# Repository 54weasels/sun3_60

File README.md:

# Homebrew Sun 3/60

This project reproduces the Sun 3/60 computer from available schematics such as https://www.sun3arc.org/schematics/3_60/index.phtml

At the moment:
- only implementing the min required 4mb of RAM
- left out the SCSI and Video sections
- only put in the serial controller for A/B, left out the keyboard/mouse
- TTL serial, I didn't implement full rs232 or modem support
- left out the coax ethernet entirely
- no FPU

The board can boot a standard boot PROM (using version XXX for development), as well as netboot SunOS 4.1.1 and NetBSD10.
NetBSD with a GENERIC kernel is not really functional because of the 4MB of RAM and swap over network.

Current version is a 4-layer board - check the build/version log in the production directory for known issues.

## TODO
- For the current board layout, at a high level
  - add more RAM - either moving to 4MB 30-pin SIMMs, or redesign around 72-pin SIMMs, or both
  - replace a few unobtainium or exceedingly cumbersome components like the bipolar PROM for the idprom
- Moving to a new layout, can add a lot more in
  - FPU
  - SCSI
  - decide on whether or not to put in video, and which one. If video goes in then so should the missing keyboard/mouse serial controller.
- Some more modernization is possible
  - add an on-board twisted pair transciever and RJ45 port
- If things really are going well, in the long term whole swaths of the low-density logic and PALs can be replaced with a/few CPLDs.

## FAQ
- What was this designed in, layers, etc?
  - This was done in KiCAD and it's a 4-layer board. It helped to have the signals easily accessible on the top and bottom to do critical fixes.
- Where is storage, and can we get some modern solution?
  - SCSI is next, but is quite big and will increase the board size by ~20%. SCSI-to-SD can be used easily. More fancy solutionsl like SCSI-to-SATA are not likely to happen.
- Can we get rid of the PALs?
  - YES, see the note on the [PAL page](pal/Readme.md)
- How about FPGAs?
  - Most likely not.
- What's the deal with video?
  - The framebuffer available in the schematics is both a bottom shelf BW, main-RAM-stealing all-in-software deal, and ECL levels on top of it. While getting it to do VGA levels is probably not that hard, it's goint to be a really bad solution overall.
  - Ideally we can get the schematics for the P4 CG4(6?) which is color and much better overall. It may be possible to reverse-engineer an existing board without the schematics, but I'm not going to do so with the only working board I have - I'll gladly buy another one to experiment with, if one was available.
- Where's the VME bus?
  - There never was a VME bus on the 3/60. It might be possible to add one, depending on how complete the various PALs are. It's unlikely due to not really having anything to add in that's not already there (Ethernet, SCSI, RAM) so unless there's a plentiful and amazing VME video card, this is not a priority.
- How about surface mount components where available, more modernization?
  - Sure! the initial implementation/layout/component choice was entirely driven by trying to be as close to the original as possible, so it's easier to debug when things go south, which they did. As the design stabilizes, it's possible to compress quite a bit, including going to higher layer count board, consolidating components like the static ram for the MMU into wider variants, etc.
- How about a processor upgrade?
  - While the original 3/60 board has room for a 68030, it's wired to run exclusively in '020 compatibility mode, and there is no way to get the built-in MMU to work.
  - It's possible to boost the main clock substantially (50Mhz which is divided by two for the CPU resulting in 25Mhz) and still have a stable system. The core design is pretty asynchronous so it might also be possible to run the RAM/etc at slower speed and run the processor faster (as you can do on the 3/80 by splitting the FPU and CPU clocks for example), but it hasn't been tried yet. It will not yield substantial improvements however.

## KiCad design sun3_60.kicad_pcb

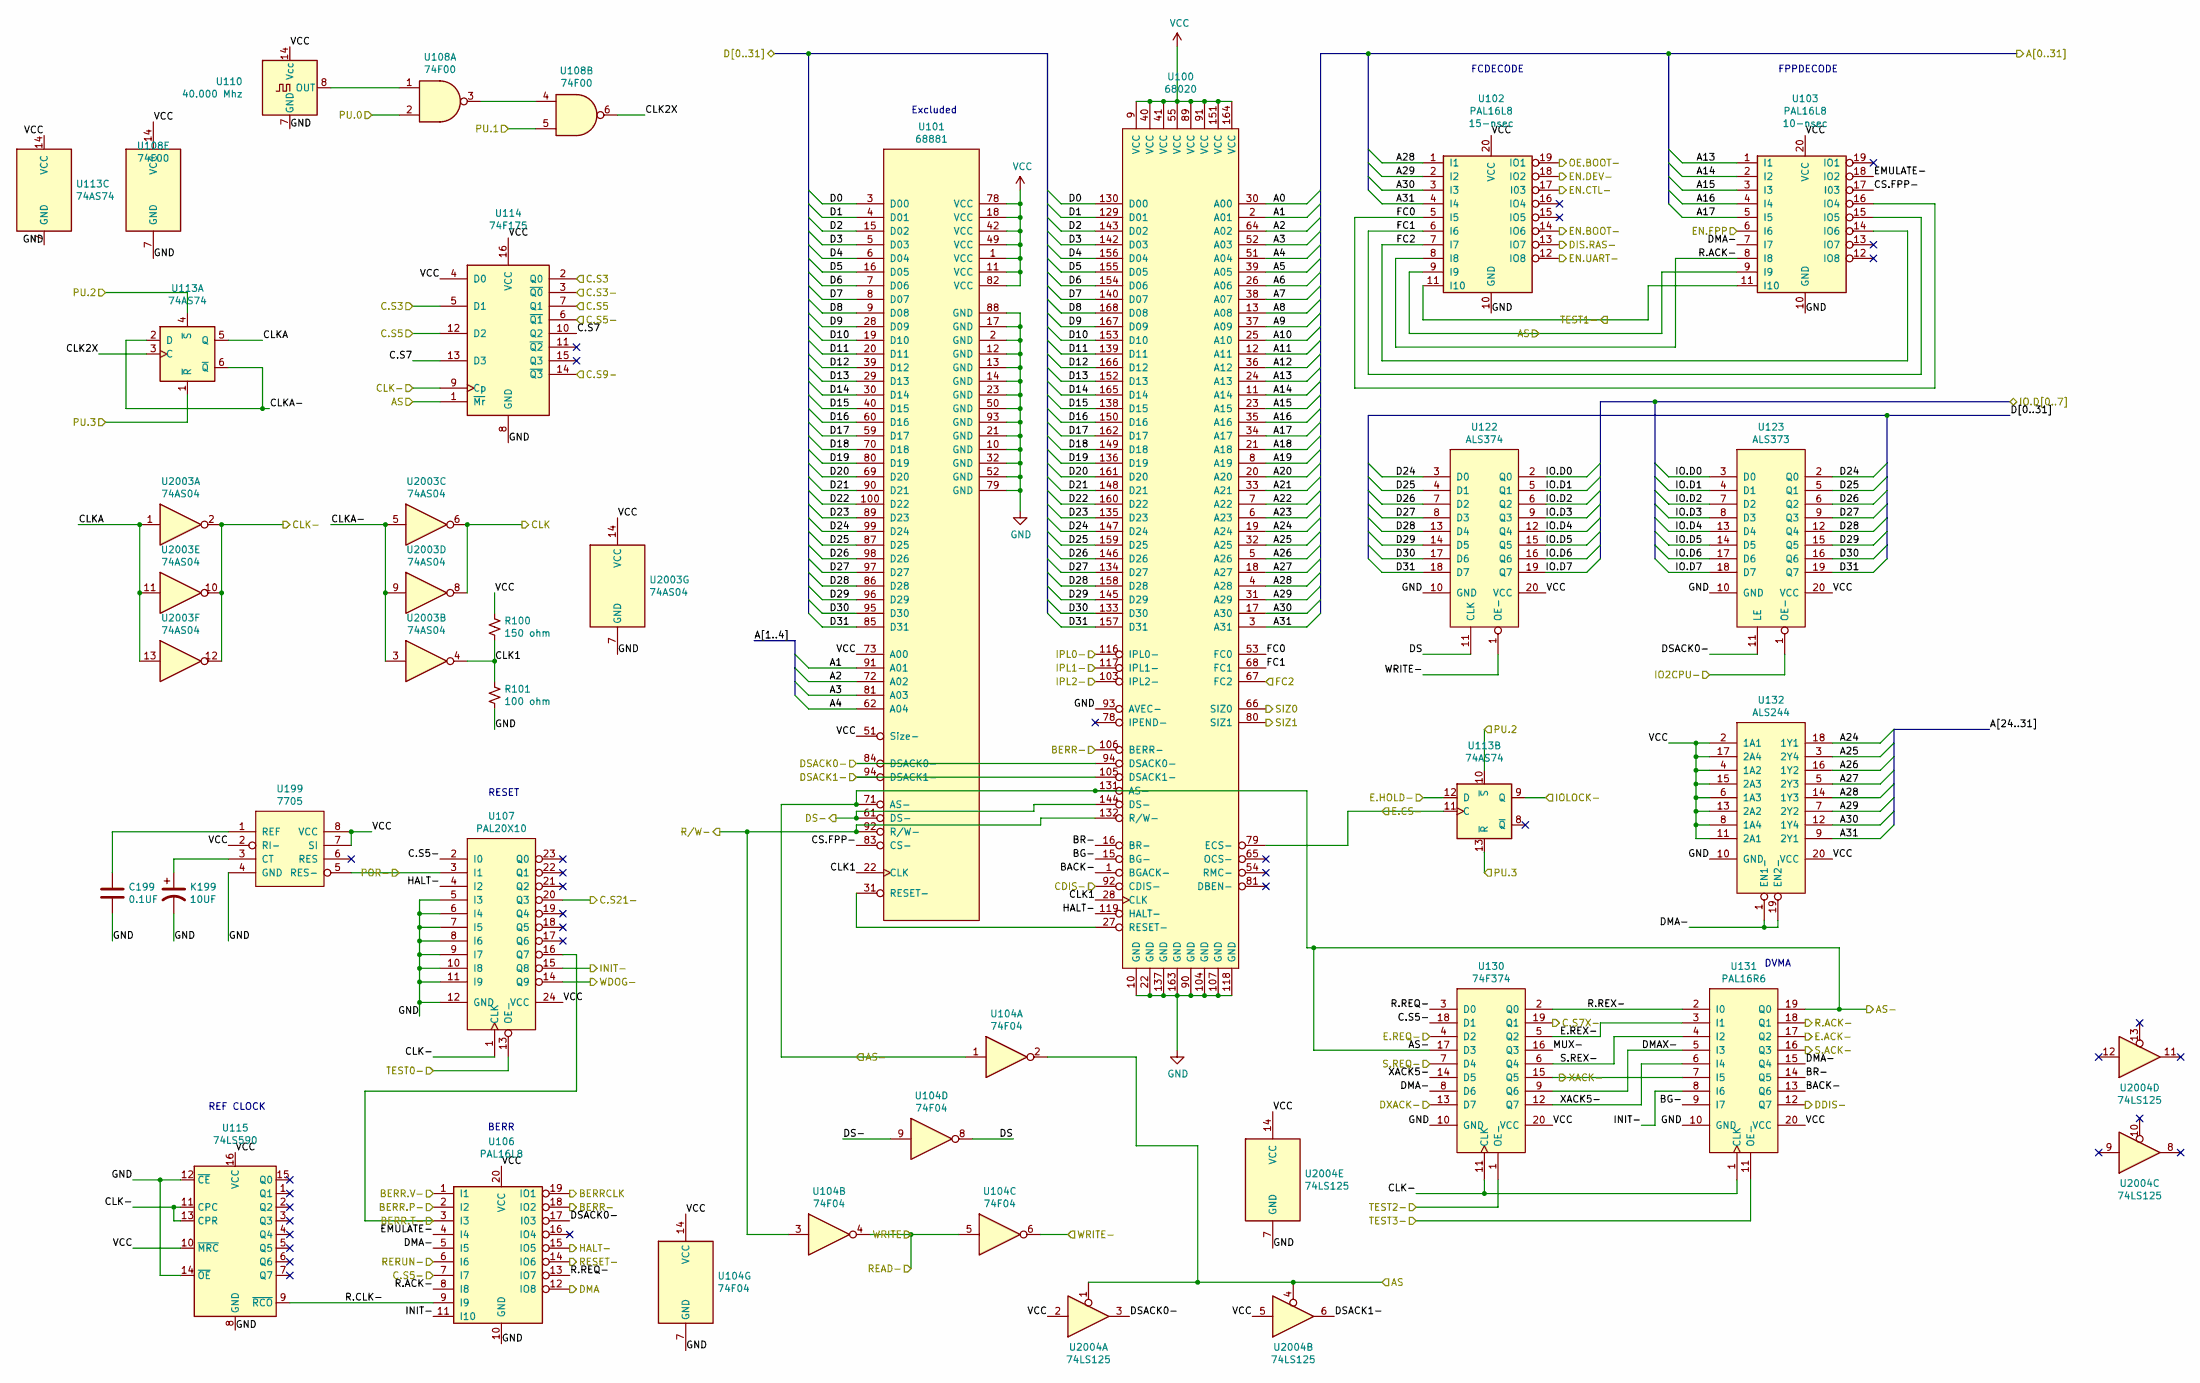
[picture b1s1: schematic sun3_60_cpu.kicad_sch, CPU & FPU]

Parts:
C199: 0.1UF; C_Disc_D3.0mm_W2.0mm_P2.50mm
K199: 10UF; CP_Radial_D10.0mm_P5.00mm
R100: 150 ohm; R_Axial_DIN0207_L6.3mm_D2.5mm_P7.62mm_Horizontal
R101: 100 ohm; R_Axial_DIN0207_L6.3mm_D2.5mm_P7.62mm_Horizontal
U100: 68020
U101: 68881
U102, U103, U106: PAL16L8; DIP-20_W7.62mm
U104: 74F04; DIP-14_W7.62mm
U107: PAL20X10; DIP-24_W7.62mm
U108: 74F00; DIP-14_W7.62mm
U110: 40.000 Mhz; Oscillator_DIP-14
U113: 74AS74; DIP-14_W7.62mm
U114: 74F175; DIP-16_W7.62mm
U115: 74LS590; DIP-16_W7.62mm
U122: ALS374; ALS373
U123: ALS373
U130: 74F374; DIP-20_W7.62mm
U131: PAL16R6; DIP-20_W7.62mm
U132: ALS244; DIP-20_W7.62mm
U199: 7705; DIP-8_W7.62mm
U2003: 74AS04; DIP-14_W7.62mm
U2004: 74LS125; DIP-14_W7.62mm

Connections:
/AS: U102.9 (I9), U103.9 (I9), U104.2, U114.1 (~Mr), U2004.1, U2004.4; also elsewhere on the board
/AS-: U100.131 (AS-), U101.71 (AS-), U104.1, U130.17 (D3), U131.19 (Q0); also elsewhere on the board
/BERR-: U100.106 (BERR-), U106.18 (IO2); also elsewhere on the board
/C.S3: U114.2 (Q0), U114.5 (D1); also elsewhere on the board
/C.S3-: U114.3 (~Q0); also elsewhere on the board
/C.S5: U114.7 (Q1), U114.12 (D2); also elsewhere on the board
/CDIS-: U100.92 (CDIS-); also elsewhere on the board
/CLK: U2003.6, U2003.8; also elsewhere on the board
/CLK-: U107.1 (CLK), U114.9 (Cp), U115.11 (CPC), U115.13 (CPR), U130.11 (CLK), U131.1 (CLK), U2003.2, U2003.10, U2003.12; also elsewhere on the board
/DDIS-: U131.12 (Q7); also elsewhere on the board
/DIS.RAS-: U102.13 (IO7); also elsewhere on the board
/DMA: U106.12 (IO8); also elsewhere on the board
/DS-: U100.144 (DS-), U101.61 (DS-), U104.9; also elsewhere on the board
/DSACK0-: U100.94 (DSACK0-), U101.84 (DSACK0-), U106.17 (I03), U123.11 (LE), U2004.3; also elsewhere on the board
/DSACK1-: U100.105 (DSACK1-), U101.94 (DSACK1-), U2004.6; also elsewhere on the board
/DXACK-: U130.13 (D7); also elsewhere on the board
/E.ACK-: U131.17 (Q2); also elsewhere on the board
/E.CS-: U100.79 (ECS-), U113.11 (C); also elsewhere on the board
/E.HOLD-: U113.12 (D); also elsewhere on the board
/E.REQ-: U130.4 (D2); also elsewhere on the board
/EN.DEV-: U102.18 (IO2); also elsewhere on the board
/EN.UART-: U102.12 (IO8); also elsewhere on the board
/Ethernet/A0: U100.30 (A00); also elsewhere on the board
/Ethernet/A1: U100.2 (A01), U101.91 (A01); also elsewhere on the board
/Ethernet/A2: U100.64 (A02), U101.72 (A02); also elsewhere on the board
/Ethernet/A3: U100.52 (A03), U101.81 (A03); also elsewhere on the board
/Ethernet/A4: U100.51 (A04), U101.62 (A04); also elsewhere on the board
/Ethernet/A5: U100.39 (A05); also elsewhere on the board
/Ethernet/A6: U100.26 (A06); also elsewhere on the board
/Ethernet/A7: U100.38 (A07); also elsewhere on the board
/Ethernet/A8: U100.13 (A08); also elsewhere on the board
/Ethernet/A9: U100.37 (A09); also elsewhere on the board
/Ethernet/A10: U100.25 (A10); also elsewhere on the board
/Ethernet/A11: U100.12 (A11); also elsewhere on the board
/Ethernet/A12: U100.36 (A12); also elsewhere on the board
/Ethernet/A13: U100.24 (A13), U103.1 (I1); also elsewhere on the board
/Ethernet/A14: U100.11 (A14), U103.2 (I2); also elsewhere on the board
/Ethernet/A15: U100.23 (A15), U103.3 (I3); also elsewhere on the board
/Ethernet/A16: U100.35 (A16), U103.4 (I4); also elsewhere on the board
/Ethernet/A17: U100.34 (A17), U103.5 (I5); also elsewhere on the board
/Ethernet/A18: U100.21 (A18); also elsewhere on the board
/Ethernet/A19: U100.8 (A19); also elsewhere on the board
/Ethernet/A20: U100.20 (A20); also elsewhere on the board
/Ethernet/A21: U100.33 (A21); also elsewhere on the board
/Ethernet/A22: U100.7 (A22); also elsewhere on the board
/Ethernet/A23: U100.6 (A23); also elsewhere on the board
/Ethernet/A24: U100.19 (A24), U132.18 (1Y1); also elsewhere on the board
/Ethernet/A25: U100.32 (A25), U132.3 (2Y4); also elsewhere on the board
/Ethernet/A26: U100.5 (A26), U132.16 (1Y2); also elsewhere on the board
/Ethernet/A27: U100.18 (A27), U132.5 (2Y3); also elsewhere on the board
/Ethernet/A28: U100.4 (A28), U102.1 (I1), U132.14 (1Y3); also elsewhere on the board
/Ethernet/A29: U100.31 (A29), U102.2 (I2), U132.7 (2Y2); also elsewhere on the board
/Ethernet/A30: U100.17 (A30), U102.3 (I3), U132.12 (1Y4); also elsewhere on the board
/Ethernet/A31: U100.3 (A31), U102.4 (I4), U132.9 (2Y1); also elsewhere on the board
/FC2: U100.67 (FC2), U102.7 (I7), U103.14 (IO6); also elsewhere on the board
/HALT-: U100.119 (HALT-), U106.15 (IO5), U107.4 (I2); also elsewhere on the board
/INIT-: U106.11 (I10), U107.15 (Q8), U131.8 (I6); also elsewhere on the board
/IO2CPU-: U123.1 (OE-); also elsewhere on the board
/IOLOCK-: U113.9 (Q); also elsewhere on the board
/IPL0-: U100.116 (IPL0-); also elsewhere on the board
/IPL1-: U100.117 (IPL1-); also elsewhere on the board
/IPL2-: U100.103 (IPL2-); also elsewhere on the board
/POR-: U107.3 (I1), U199.5 (RES-); also elsewhere on the board
/PU0: U108.2; also elsewhere on the board
/PU1: U108.5; also elsewhere on the board
/PU2: U113.4 (~S), U113.10 (~S); also elsewhere on the board
/PU3: U113.1 (~R), U113.13 (~R); also elsewhere on the board
/R.ACK-: U102.8 (I8), U103.8 (I8), U106.8 (I8), U131.18 (Q1); also elsewhere on the board
/READ-: U104.4, U104.5; also elsewhere on the board
/RERUN-: U106.6 (I6); also elsewhere on the board
/RESET-: U106.14 (IO6); also elsewhere on the board
/R/W-: U100.132 (R/W-), U101.92 (R/W-), U104.3; also elsewhere on the board
/SCSI 2, Parity/IO.D0: U122.2 (Q0), U123.3 (D0); also elsewhere on the board
/SCSI 2, Parity/IO.D1: U122.5 (Q1), U123.4 (D1); also elsewhere on the board
/SCSI 2, Parity/IO.D2: U122.6 (Q2), U123.7 (D2); also elsewhere on the board
/SCSI 2, Parity/IO.D3: U122.9 (Q3), U123.8 (D3); also elsewhere on the board
/SCSI 2, Parity/IO.D4: U122.12 (Q4), U123.13 (D4); also elsewhere on the board
/SCSI 2, Parity/IO.D5: U122.15 (Q5), U123.14 (D5); also elsewhere on the board
/SCSI 2, Parity/IO.D6: U122.16 (Q6), U123.17 (D6); also elsewhere on the board
/SCSI 2, Parity/IO.D7: U122.19 (Q7), U123.18 (D7); also elsewhere on the board
/SIZ0: U100.66 (SIZ0); also elsewhere on the board
/SIZ1: U100.80 (SIZ1); also elsewhere on the board
/TEST0-: U107.13 (OE-); also elsewhere on the board
/TEST1-: U102.11 (I10), U103.11 (I10); also elsewhere on the board
/TEST2-: U130.1 (OE-); also elsewhere on the board
/TEST3-: U131.11 (OE-); also elsewhere on the board
/WDOG-: U107.14 (Q9); also elsewhere on the board
/WRITE-: U104.6, U122.1 (OE-); also elsewhere on the board
/XACK-: U130.15 (Q5), U131.7 (I5); also elsewhere on the board
/sun3_60_cpu/BACK-: U100.1 (BGACK-), U131.13 (Q6)
/sun3_60_cpu/BERR.P-: U106.2 (I2); also elsewhere on the board
/sun3_60_cpu/BERR.T-: U106.3 (I3), U107.16 (Q7); also elsewhere on the board
/sun3_60_cpu/BERR.V-: U106.1 (I1); also elsewhere on the board
/sun3_60_cpu/BERRCLK: U106.19 (IO1); also elsewhere on the board
/sun3_60_cpu/BG-: U100.15 (BG-), U131.9 (I7)
/sun3_60_cpu/BR-: U100.16 (BR-), U131.14 (Q5)
/sun3_60_cpu/C.S5-: U106.7 (I7), U107.2 (I0), U114.6 (~Q1), U130.18 (D1); also elsewhere on the board
/sun3_60_cpu/C.S7: U114.10 (Q2), U114.13 (D3)
/sun3_60_cpu/C.S7X-: U130.19 (Q1); also elsewhere on the board
/sun3_60_cpu/C.S9-: U114.14 (~Q3); also elsewhere on the board
/sun3_60_cpu/C.S21-: U107.20 (Q3); also elsewhere on the board
/sun3_60_cpu/CLK1: R100.2, R101.1, U100.28 (CLK), U101.22 (CLK), U2003.4
/sun3_60_cpu/CLK2X: U108.6, U113.3 (C)
/sun3_60_cpu/CLKA: U113.5 (Q), U2003.1, U2003.11, U2003.13
/sun3_60_cpu/CLKA-: U113.2 (D), U113.6 (~Q), U2003.3, U2003.5, U2003.9
/sun3_60_cpu/CS.FPP-: U101.83 (CS-), U103.17 (I03)
/sun3_60_cpu/D0: U100.130 (D00), U101.3 (D00); also elsewhere on the board
/sun3_60_cpu/D1: U100.129 (D01), U101.4 (D01); also elsewhere on the board
/sun3_60_cpu/D2: U100.143 (D02), U101.15 (D02); also elsewhere on the board
/sun3_60_cpu/D3: U100.142 (D03), U101.5 (D03); also elsewhere on the board
/sun3_60_cpu/D4: U100.156 (D04), U101.6 (D04); also elsewhere on the board
/sun3_60_cpu/D5: U100.155 (D05), U101.16 (D05); also elsewhere on the board
/sun3_60_cpu/D6: U100.154 (D06), U101.7 (D06); also elsewhere on the board
/sun3_60_cpu/D7: U100.140 (D07), U101.8 (D07); also elsewhere on the board
/sun3_60_cpu/D8: U100.168 (D08), U101.9 (D08); also elsewhere on the board
/sun3_60_cpu/D9: U100.167 (D09), U101.28 (D09); also elsewhere on the board
/sun3_60_cpu/D10: U100.153 (D10), U101.19 (D10); also elsewhere on the board
/sun3_60_cpu/D11: U100.139 (D11), U101.20 (D11); also elsewhere on the board
/sun3_60_cpu/D12: U100.166 (D12), U101.39 (D12); also elsewhere on the board
/sun3_60_cpu/D13: U100.152 (D13), U101.29 (D13); also elsewhere on the board
/sun3_60_cpu/D14: U100.165 (D14), U101.30 (D14); also elsewhere on the board
/sun3_60_cpu/D15: U100.138 (D15), U101.40 (D15); also elsewhere on the board
/sun3_60_cpu/D16: U100.150 (D16), U101.60 (D16); also elsewhere on the board
/sun3_60_cpu/D17: U100.162 (D17), U101.59 (D17); also elsewhere on the board
/sun3_60_cpu/D18: U100.149 (D18), U101.70 (D18); also elsewhere on the board
/sun3_60_cpu/D19: U100.136 (D19), U101.80 (D19); also elsewhere on the board
/sun3_60_cpu/D20: U100.161 (D20), U101.69 (D20); also elsewhere on the board
/sun3_60_cpu/D21: U100.148 (D21), U101.90 (D21); also elsewhere on the board
/sun3_60_cpu/D22: U100.160 (D22), U101.100 (D22); also elsewhere on the board
/sun3_60_cpu/D23: U100.135 (D23), U101.89 (D23); also elsewhere on the board
/sun3_60_cpu/D24: U100.147 (D24), U101.99 (D24), U122.3 (D0), U123.2 (Q0); also elsewhere on the board
/sun3_60_cpu/D25: U100.159 (D25), U101.87 (D25), U122.4 (D1), U123.5 (Q1); also elsewhere on the board
/sun3_60_cpu/D26: U100.146 (D26), U101.98 (D26), U122.7 (D2), U123.6 (Q2); also elsewhere on the board
/sun3_60_cpu/D27: U100.134 (D27), U101.97 (D27), U122.8 (D3), U123.9 (Q3); also elsewhere on the board
/sun3_60_cpu/D28: U100.158 (D28), U101.86 (D28), U122.13 (D4), U123.12 (Q4); also elsewhere on the board
/sun3_60_cpu/D29: U100.145 (D29), U101.96 (D29), U122.14 (D5), U123.15 (Q5); also elsewhere on the board
/sun3_60_cpu/D30: U100.133 (D30), U101.95 (D30), U122.17 (D6), U123.16 (Q6); also elsewhere on the board
/sun3_60_cpu/D31: U100.157 (D31), U101.85 (D31), U122.18 (D7), U123.19 (Q7); also elsewhere on the board
/sun3_60_cpu/DMA-: U103.7 (I7), U106.5 (I5), U130.8 (D6), U131.15 (Q4), U132.1 (EN1-), U132.19 (EN2-)
/sun3_60_cpu/DMAX-: U130.9 (Q6), U131.5 (I3)
/sun3_60_cpu/DS: U104.8, U122.11 (CLK)
/sun3_60_cpu/E.REX-: U130.5 (Q2), U131.3 (I1)
/sun3_60_cpu/EMULATE-: U103.18 (IO2), U106.4 (I4)
/sun3_60_cpu/EN.BOOT-: U102.14 (IO6); also elsewhere on the board
/sun3_60_cpu/EN.CTL-: U102.17 (I03); also elsewhere on the board
/sun3_60_cpu/EN.FPP: U103.6 (I6); also elsewhere on the board
/sun3_60_cpu/FC0: U100.53 (FC0), U102.5 (I5), U103.16 (IO4)
/sun3_60_cpu/FC1: U100.68 (FC1), U102.6 (I6), U103.15 (IO5)
/sun3_60_cpu/MUX-: U130.16 (Q3)
/sun3_60_cpu/OE.BOOT-: U102.19 (IO1); also elsewhere on the board
/sun3_60_cpu/R.CLK-: U106.9 (I9), U115.9 (~RCO)
/sun3_60_cpu/R.REQ-: U106.13 (IO7), U130.3 (D0)
/sun3_60_cpu/R.REX-: U130.2 (Q0), U131.2 (I0)
/sun3_60_cpu/S.ACK-: U131.16 (Q3)
/sun3_60_cpu/S.REQ-: U130.7 (D4)
/sun3_60_cpu/S.REX-: U130.6 (Q4), U131.4 (I2)
/sun3_60_cpu/XACK5-: U130.12 (Q7), U130.14 (D5), U131.6 (I4)
GND: C199.2, K199.2, R101.2, U100.10 (GND), U100.22 (GND), U100.90 (GND), U100.93 (AVEC-), U100.104 (GND), U100.107 (GND), U100.118 (GND), U100.137 (GND), U100.163 (GND), U101.2 (GND), U101.10 (GND), U101.12 (GND), U101.13 (GND), U101.14 (GND), U101.17 (GND), U101.21 (GND), U101.23 (GND), U101.32 (GND), U101.50 (GND), U101.52 (GND), U101.79 (GND), U101.88 (GND), U101.93 (GND), U102.10 (GND), U103.10 (GND), U104.7 (GND), U106.10 (GND), U107.5 (I3), U107.6 (I4), U107.7 (I5), U107.8 (I6), U107.9 (I7), U107.10 (I8), U107.11 (I9), U107.12 (GND), U108.7 (GND), U110.7 (GND), U113.7 (GND), U114.8 (GND), U115.8 (GND), U115.12 (~CE), U115.14 (~OE), U122.10 (GND), U123.10 (GND), U130.10 (GND), U131.10 (GND), U132.10 (GND), U199.4 (GND), U2003.7 (GND), U2004.7 (GND); also elsewhere on the board
unnamed: U100.27 (RESET-), U101.31 (RESET-)
unnamed: U108.3, U108.4
unnamed: U108.1, U110.8 (OUT)
unnamed: K199.1, U199.3 (CT)
unnamed: C199.1, U199.1 (REF)
VCC: R100.1, U100.9 (VCC), U100.40 (VCC), U100.41 (VCC), U100.55 (VCC), U100.89 (VCC), U100.91 (VCC), U100.151 (VCC), U100.164 (VCC), U101.1 (VCC), U101.11 (VCC), U101.18 (VCC), U101.42 (VCC), U101.49 (VCC), U101.51 (Size-), U101.73 (A00), U101.78 (VCC), U101.82 (VCC), U102.20 (VCC), U103.20 (VCC), U104.14 (VCC), U106.20 (VCC), U107.24 (VCC), U108.14 (VCC), U110.14 (Vcc), U113.14 (VCC), U114.4 (D0), U114.16 (VCC), U115.10 (~MRC), U115.16 (VCC), U122.20 (VCC), U123.20 (VCC), U130.20 (VCC), U131.20 (VCC), U132.2 (1A1), U132.4 (1A2), U132.6 (1A3), U132.8 (1A4), U132.11 (2A1), U132.13 (2A2), U132.15 (2A3), U132.17 (2A4), U132.20 (VCC), U199.2 (RI-), U199.7 (SI), U199.8 (VCC), U2003.14 (VCC), U2004.2, U2004.5, U2004.14 (VCC); also elsewhere on the board

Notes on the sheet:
REF CLOCK
BERR
FCDECODE
DVMA
Excluded
FPPDECODE
RESET

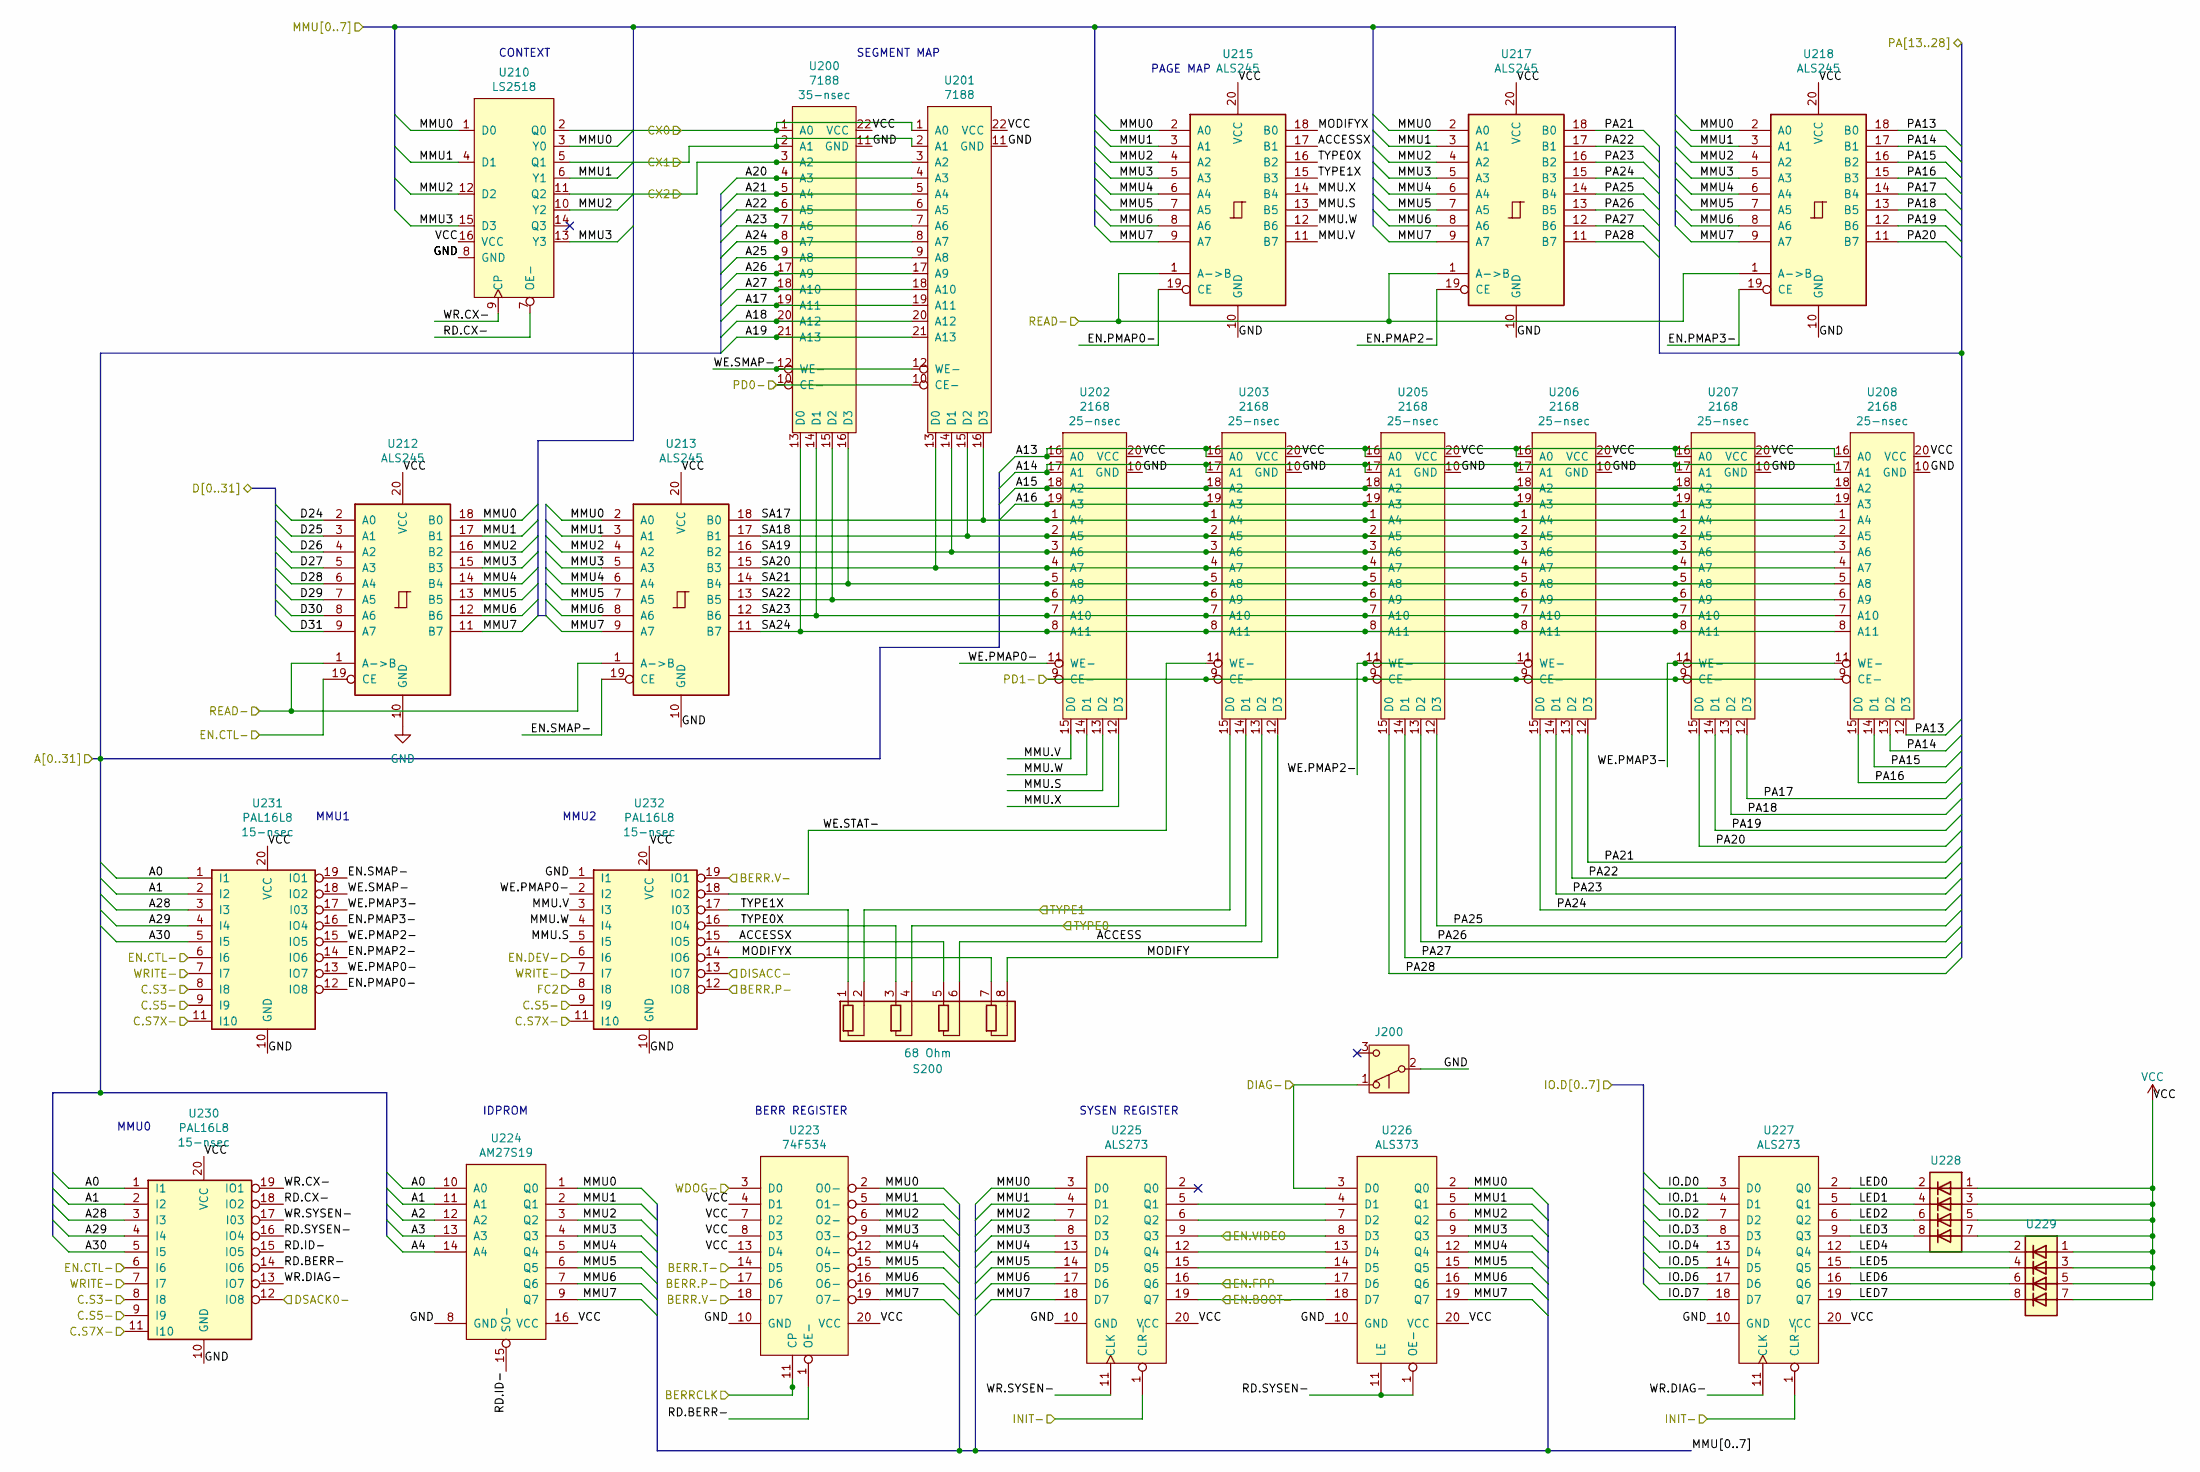
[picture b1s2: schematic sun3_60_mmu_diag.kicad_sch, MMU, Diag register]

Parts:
J200: DIAG; PinHeader_1x03_P2.54mm_Vertical
S200: 68 Ohm; R_Array_SIP8
U200, U201: 7188
U202, U203, U205, U206, U207, U208: 2168
U210: LS2518
U212, U213, U215, U217, U218: ALS245
U223: 74F534; DIP-20_W7.62mm
U224: AM27S19
U225, U227: ALS273
U226: ALS373
U228, U229: LED_Block; PinHeader_2x04_P2.54mm_Vertical
U230, U231, U232: PAL16L8; DIP-20_W7.62mm

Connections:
/C.S3-: U230.8 (I8), U231.8 (I8); also elsewhere on the board
/CX0: U200.1 (A0), U201.1 (A0), U210.2 (Q0); also elsewhere on the board
/CX1: U200.2 (A1), U201.2 (A1), U210.5 (Q1); also elsewhere on the board
/CX2: U200.3 (A2), U201.3 (A2), U210.11 (Q2); also elsewhere on the board
/DIAG-: J200.1 (A), U226.3 (D0); also elsewhere on the board
/DISACC-: U232.13 (IO7); also elsewhere on the board
/DSACK0-: U230.12 (IO8); also elsewhere on the board
/EN.DEV-: U232.6 (I6); also elsewhere on the board
/Ethernet/A0: U224.10 (A0), U230.1 (I1), U231.1 (I1); also elsewhere on the board
/Ethernet/A1: U224.11 (A1), U230.2 (I2), U231.2 (I2); also elsewhere on the board
/Ethernet/A2: U224.12 (A2); also elsewhere on the board
/Ethernet/A3: U224.13 (A3); also elsewhere on the board
/Ethernet/A4: U224.14 (A4); also elsewhere on the board
/Ethernet/A13: U202.16 (A0), U203.16 (A0), U205.16 (A0), U206.16 (A0), U207.16 (A0), U208.16 (A0); also elsewhere on the board
/Ethernet/A14: U202.17 (A1), U203.17 (A1), U205.17 (A1), U206.17 (A1), U207.17 (A1), U208.17 (A1); also elsewhere on the board
/Ethernet/A15: U202.18 (A2), U203.18 (A2), U205.18 (A2), U206.18 (A2), U207.18 (A2), U208.18 (A2); also elsewhere on the board
/Ethernet/A16: U202.19 (A3), U203.19 (A3), U205.19 (A3), U206.19 (A3), U207.19 (A3), U208.19 (A3); also elsewhere on the board
/Ethernet/A17: U200.19 (A11), U201.19 (A11); also elsewhere on the board
/Ethernet/A18: U200.20 (A12), U201.20 (A12); also elsewhere on the board
/Ethernet/A19: U200.21 (A13), U201.21 (A13); also elsewhere on the board
/Ethernet/A20: U200.4 (A3), U201.4 (A3); also elsewhere on the board
/Ethernet/A21: U200.5 (A4), U201.5 (A4); also elsewhere on the board
/Ethernet/A22: U200.6 (A5), U201.6 (A5); also elsewhere on the board
/Ethernet/A23: U200.7 (A6), U201.7 (A6); also elsewhere on the board
/Ethernet/A24: U200.8 (A7), U201.8 (A7); also elsewhere on the board
/Ethernet/A25: U200.9 (A8), U201.9 (A8); also elsewhere on the board
/Ethernet/A26: U200.17 (A9), U201.17 (A9); also elsewhere on the board
/Ethernet/A27: U200.18 (A10), U201.18 (A10); also elsewhere on the board
/Ethernet/A28: U230.3 (I3), U231.3 (I3); also elsewhere on the board
/Ethernet/A29: U230.4 (I4), U231.4 (I4); also elsewhere on the board
/Ethernet/A30: U230.5 (I5), U231.5 (I5); also elsewhere on the board
/FC2: U232.8 (I8); also elsewhere on the board
/INIT-: U225.1 (CLR-), U227.1 (CLR-); also elsewhere on the board
/PD0-: U200.10 (CE-), U201.10 (CE-); also elsewhere on the board
/PD1-: U202.9 (CE-), U203.9 (CE-), U205.9 (CE-), U206.9 (CE-), U207.9 (CE-), U208.9 (CE-); also elsewhere on the board
/READ-: U212.1 (A->B), U213.1 (A->B), U215.1 (A->B), U217.1 (A->B), U218.1 (A->B); also elsewhere on the board
/S8A Memory/PA13: U208.12 (D3), U218.18 (B0); also elsewhere on the board
/S8A Memory/PA14: U208.13 (D2), U218.17 (B1); also elsewhere on the board
/S8A Memory/PA15: U208.14 (D1), U218.16 (B2); also elsewhere on the board
/S8A Memory/PA16: U208.15 (D0), U218.15 (B3); also elsewhere on the board
/S8A Memory/PA17: U207.12 (D3), U218.14 (B4); also elsewhere on the board
/S8A Memory/PA18: U207.13 (D2), U218.13 (B5); also elsewhere on the board
/S8A Memory/PA19: U207.14 (D1), U218.12 (B6); also elsewhere on the board
/S8A Memory/PA20: U207.15 (D0), U218.11 (B7); also elsewhere on the board
/S8A Memory/PA21: U206.12 (D3), U217.18 (B0); also elsewhere on the board
/S8A Memory/PA22: U206.13 (D2), U217.17 (B1); also elsewhere on the board
/S8A Memory/PA23: U206.14 (D1), U217.16 (B2); also elsewhere on the board
/S8A Memory/PA24: U206.15 (D0), U217.15 (B3); also elsewhere on the board
/S8A Memory/PA25: U205.12 (D3), U217.14 (B4); also elsewhere on the board
/S8A Memory/PA26: U205.13 (D2), U217.13 (B5); also elsewhere on the board
/S8A Memory/PA27: U205.14 (D1), U217.12 (B6); also elsewhere on the board
/S8A Memory/PA28: U205.15 (D0), U217.11 (B7); also elsewhere on the board
/SCSI 2, Parity/IO.D0: U227.3 (D0); also elsewhere on the board
/SCSI 2, Parity/IO.D1: U227.4 (D1); also elsewhere on the board
/SCSI 2, Parity/IO.D2: U227.7 (D2); also elsewhere on the board
/SCSI 2, Parity/IO.D3: U227.8 (D3); also elsewhere on the board
/SCSI 2, Parity/IO.D4: U227.13 (D4); also elsewhere on the board
/SCSI 2, Parity/IO.D5: U227.14 (D5); also elsewhere on the board
/SCSI 2, Parity/IO.D6: U227.17 (D6); also elsewhere on the board
/SCSI 2, Parity/IO.D7: U227.18 (D7); also elsewhere on the board
/WDOG-: U223.3 (D0); also elsewhere on the board
/WRITE-: U230.7 (I7), U231.7 (I7), U232.7 (I7); also elsewhere on the board
/sun3_60_cpu/BERR.P-: U223.17 (D6), U232.12 (IO8); also elsewhere on the board
/sun3_60_cpu/BERR.T-: U223.14 (D5); also elsewhere on the board
/sun3_60_cpu/BERR.V-: U223.18 (D7), U232.19 (IO1); also elsewhere on the board
/sun3_60_cpu/BERRCLK: U223.11 (CP); also elsewhere on the board
/sun3_60_cpu/C.S5-: U230.9 (I9), U231.9 (I9), U232.9 (I9); also elsewhere on the board
/sun3_60_cpu/C.S7X-: U230.11 (I10), U231.11 (I10), U232.11 (I10); also elsewhere on the board
/sun3_60_cpu/D24: U212.2 (A0); also elsewhere on the board
/sun3_60_cpu/D25: U212.3 (A1); also elsewhere on the board
/sun3_60_cpu/D26: U212.4 (A2); also elsewhere on the board
/sun3_60_cpu/D27: U212.5 (A3); also elsewhere on the board
/sun3_60_cpu/D28: U212.6 (A4); also elsewhere on the board
/sun3_60_cpu/D29: U212.7 (A5); also elsewhere on the board
/sun3_60_cpu/D30: U212.8 (A6); also elsewhere on the board
/sun3_60_cpu/D31: U212.9 (A7); also elsewhere on the board
/sun3_60_cpu/EN.BOOT-: U225.19 (Q7), U226.18 (D7); also elsewhere on the board
/sun3_60_cpu/EN.CTL-: U212.19 (CE), U230.6 (I6), U231.6 (I6); also elsewhere on the board
/sun3_60_cpu/EN.FPP: U225.16 (Q6), U226.17 (D6); also elsewhere on the board
/sun3_60_eeprom/TYPE0: S200.4 (R2.2), U203.14 (D1); also elsewhere on the board
/sun3_60_eeprom/TYPE1: S200.2 (R1.2), U203.15 (D0); also elsewhere on the board
/sun3_60_mmu_diag/ACCESS: S200.6 (R3.2), U203.13 (D2)
/sun3_60_mmu_diag/ACCESSX: S200.5 (R3.1), U215.17 (B1), U232.15 (IO5)
/sun3_60_mmu_diag/EN.PMAP0-: U215.19 (CE), U231.12 (IO8)
/sun3_60_mmu_diag/EN.PMAP2-: U217.19 (CE), U231.14 (IO6)
/sun3_60_mmu_diag/EN.PMAP3-: U218.19 (CE), U231.16 (IO4)
/sun3_60_mmu_diag/EN.SMAP-: U213.19 (CE), U231.19 (IO1)
/sun3_60_mmu_diag/EN.VIDEO: U225.9 (Q3), U226.8 (D3)
/sun3_60_mmu_diag/LED0: U227.2 (Q0), U228.2 (K)
/sun3_60_mmu_diag/LED1: U227.5 (Q1), U228.4
/sun3_60_mmu_diag/LED2: U227.6 (Q2), U228.6 (K)
/sun3_60_mmu_diag/LED3: U227.9 (Q3), U228.8 (K)
/sun3_60_mmu_diag/LED4: U227.12 (Q4), U229.2 (K)
/sun3_60_mmu_diag/LED5: U227.15 (Q5), U229.4
/sun3_60_mmu_diag/LED6: U227.16 (Q6), U229.6 (K)
/sun3_60_mmu_diag/LED7: U227.19 (Q7), U229.8 (K)
/sun3_60_mmu_diag/MMU0: U210.1 (D0), U210.3 (Y0), U212.18 (B0), U213.2 (A0), U215.2 (A0), U217.2 (A0), U218.2 (A0), U223.2 (O0-), U224.1 (Q0), U225.3 (D0), U226.2 (Q0); also elsewhere on the board
/sun3_60_mmu_diag/MMU1: U210.4 (D1), U210.6 (Y1), U212.17 (B1), U213.3 (A1), U215.3 (A1), U217.3 (A1), U218.3 (A1), U223.5 (O1-), U224.2 (Q1), U225.4 (D1), U226.5 (Q1); also elsewhere on the board
/sun3_60_mmu_diag/MMU2: U210.10 (Y2), U210.12 (D2), U212.16 (B2), U213.4 (A2), U215.4 (A2), U217.4 (A2), U218.4 (A2), U223.6 (O2-), U224.3 (Q2), U225.7 (D2), U226.6 (Q2); also elsewhere on the board
/sun3_60_mmu_diag/MMU3: U210.13 (Y3), U210.15 (D3), U212.15 (B3), U213.5 (A3), U215.5 (A3), U217.5 (A3), U218.5 (A3), U223.9 (O3-), U224.4 (Q3), U225.8 (D3), U226.9 (Q3); also elsewhere on the board
/sun3_60_mmu_diag/MMU4: U212.14 (B4), U213.6 (A4), U215.6 (A4), U217.6 (A4), U218.6 (A4), U223.12 (O4-), U224.5 (Q4), U225.13 (D4), U226.12 (Q4); also elsewhere on the board
/sun3_60_mmu_diag/MMU5: U212.13 (B5), U213.7 (A5), U215.7 (A5), U217.7 (A5), U218.7 (A5), U223.15 (O5-), U224.6 (Q5), U225.14 (D5), U226.15 (Q5); also elsewhere on the board
/sun3_60_mmu_diag/MMU6: U212.12 (B6), U213.8 (A6), U215.8 (A6), U217.8 (A6), U218.8 (A6), U223.16 (O6-), U224.7 (Q6), U225.17 (D6), U226.16 (Q6); also elsewhere on the board
/sun3_60_mmu_diag/MMU7: U212.11 (B7), U213.9 (A7), U215.9 (A7), U217.9 (A7), U218.9 (A7), U223.19 (O7-), U224.9 (Q7), U225.18 (D7), U226.19 (Q7); also elsewhere on the board
/sun3_60_mmu_diag/MMU.S: U202.13 (D2), U215.13 (B5), U232.5 (I5)
/sun3_60_mmu_diag/MMU.V: U202.15 (D0), U215.11 (B7), U232.3 (I3)
/sun3_60_mmu_diag/MMU.W: U202.14 (D1), U215.12 (B6), U232.4 (I4)
/sun3_60_mmu_diag/MMU.X: U202.12 (D3), U215.14 (B4)
/sun3_60_mmu_diag/MODIFY: S200.8 (R4.2), U203.12 (D3)
/sun3_60_mmu_diag/MODIFYX: S200.7 (R4.1), U215.18 (B0), U232.14 (IO6)
/sun3_60_mmu_diag/RD.BERR-: U223.1 (OE-), U230.14 (IO6)
/sun3_60_mmu_diag/RD.CX-: U210.7 (OE-), U230.18 (IO2)
/sun3_60_mmu_diag/RD.ID-: U224.15 (SO-), U230.15 (IO5)
/sun3_60_mmu_diag/RD.SYSEN-: U226.1 (OE-), U226.11 (LE), U230.16 (IO4)
/sun3_60_mmu_diag/SA17: U201.16 (D3), U202.1 (A4), U203.1 (A4), U205.1 (A4), U206.1 (A4), U207.1 (A4), U208.1 (A4), U213.18 (B0)
/sun3_60_mmu_diag/SA18: U201.15 (D2), U202.2 (A5), U203.2 (A5), U205.2 (A5), U206.2 (A5), U207.2 (A5), U208.2 (A5), U213.17 (B1)
/sun3_60_mmu_diag/SA19: U201.14 (D1), U202.3 (A6), U203.3 (A6), U205.3 (A6), U206.3 (A6), U207.3 (A6), U208.3 (A6), U213.16 (B2)
/sun3_60_mmu_diag/SA20: U201.13 (D0), U202.4 (A7), U203.4 (A7), U205.4 (A7), U206.4 (A7), U207.4 (A7), U208.4 (A7), U213.15 (B3)
/sun3_60_mmu_diag/SA21: U200.16 (D3), U202.5 (A8), U203.5 (A8), U205.5 (A8), U206.5 (A8), U207.5 (A8), U208.5 (A8), U213.14 (B4)
/sun3_60_mmu_diag/SA22: U200.15 (D2), U202.6 (A9), U203.6 (A9), U205.6 (A9), U206.6 (A9), U207.6 (A9), U208.6 (A9), U213.13 (B5)
/sun3_60_mmu_diag/SA23: U200.14 (D1), U202.7 (A10), U203.7 (A10), U205.7 (A10), U206.7 (A10), U207.7 (A10), U208.7 (A10), U213.12 (B6)
/sun3_60_mmu_diag/SA24: U200.13 (D0), U202.8 (A11), U203.8 (A11), U205.8 (A11), U206.8 (A11), U207.8 (A11), U208.8 (A11), U213.11 (B7)
/sun3_60_mmu_diag/TYPE0X: S200.3 (R2.1), U215.16 (B2), U232.16 (IO4)
/sun3_60_mmu_diag/TYPE1X: S200.1 (R1.1), U215.15 (B3), U232.17 (I03)
/sun3_60_mmu_diag/WE.PMAP0-: U202.11 (WE-), U231.13 (IO7), U232.2 (I2)
/sun3_60_mmu_diag/WE.PMAP2-: U205.11 (WE-), U206.11 (WE-), U231.15 (IO5)
/sun3_60_mmu_diag/WE.PMAP3-: U207.11 (WE-), U208.11 (WE-), U231.17 (I03)
/sun3_60_mmu_diag/WE.SMAP-: U200.12 (WE-), U201.12 (WE-), U231.18 (IO2)
/sun3_60_mmu_diag/WE.STAT-: U203.11 (WE-), U232.18 (IO2)
/sun3_60_mmu_diag/WR.CX-: U210.9 (CP), U230.19 (IO1)
/sun3_60_mmu_diag/WR.DIAG-: U227.11 (CLK), U230.13 (IO7)
/sun3_60_mmu_diag/WR.SYSEN-: U225.11 (CLK), U230.17 (I03)
GND: J200.2 (B), U200.11 (GND), U201.11 (GND), U202.10 (GND), U203.10 (GND), U205.10 (GND), U206.10 (GND), U207.10 (GND), U208.10 (GND), U210.8 (GND), U212.10 (GND), U213.10 (GND), U215.10 (GND), U217.10 (GND), U218.10 (GND), U223.10 (GND), U224.8 (GND), U225.10 (GND), U226.10 (GND), U227.10 (GND), U230.10 (GND), U231.10 (GND), U232.1 (I1), U232.10 (GND); also elsewhere on the board
unnamed: U225.5 (Q1), U226.4 (D1)
unnamed: U225.6 (Q2), U226.7 (D2)
unnamed: U225.12 (Q4), U226.13 (D4)
unnamed: U225.15 (Q5), U226.14 (D5)
VCC: U200.22 (VCC), U201.22 (VCC), U202.20 (VCC), U203.20 (VCC), U205.20 (VCC), U206.20 (VCC), U207.20 (VCC), U208.20 (VCC), U210.16 (VCC), U212.20 (VCC), U213.20 (VCC), U215.20 (VCC), U217.20 (VCC), U218.20 (VCC), U223.4 (D1), U223.7 (D2), U223.8 (D3), U223.13 (D4), U223.20 (VCC), U224.16 (VCC), U225.20 (VCC), U226.20 (VCC), U227.20 (VCC), U228.1 (A), U228.3 (A), U228.5, U228.7, U229.1 (A), U229.3 (A), U229.5, U229.7, U230.20 (VCC), U231.20 (VCC), U232.20 (VCC); also elsewhere on the board

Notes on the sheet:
IDPROM
SYSEN REGISTER
PAGE MAP
MMU2
BERR REGISTER
CONTEXT
MMU0
SEGMENT MAP
MMU1
